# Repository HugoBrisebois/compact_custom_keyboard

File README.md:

## Compact Custom Keyboard

This is a compact Keyboard the is powered by a raspberry pi pico and is a hotswapable kailth choc mini keyswitches, the keyboard also has LEDs that can be used for a aestetic lighting and as light to see what you are typing.
The Keyboard is also a 60% keyboard meaning that it is quite small while not having too many layers like a 40% one.

# Features
- powered by a raspberry pi pico
- RGB LEDs
- kailth choc mini keyswitches
- 3d Printed keyswitches

# Reason for build this project
i wanted a keyboard that is completely custom to me and is also something that i can use in a cyberdeck project that i want to build later on. this keyboard is also perfect for everyday use and i am looking forward to using this keyboard too.

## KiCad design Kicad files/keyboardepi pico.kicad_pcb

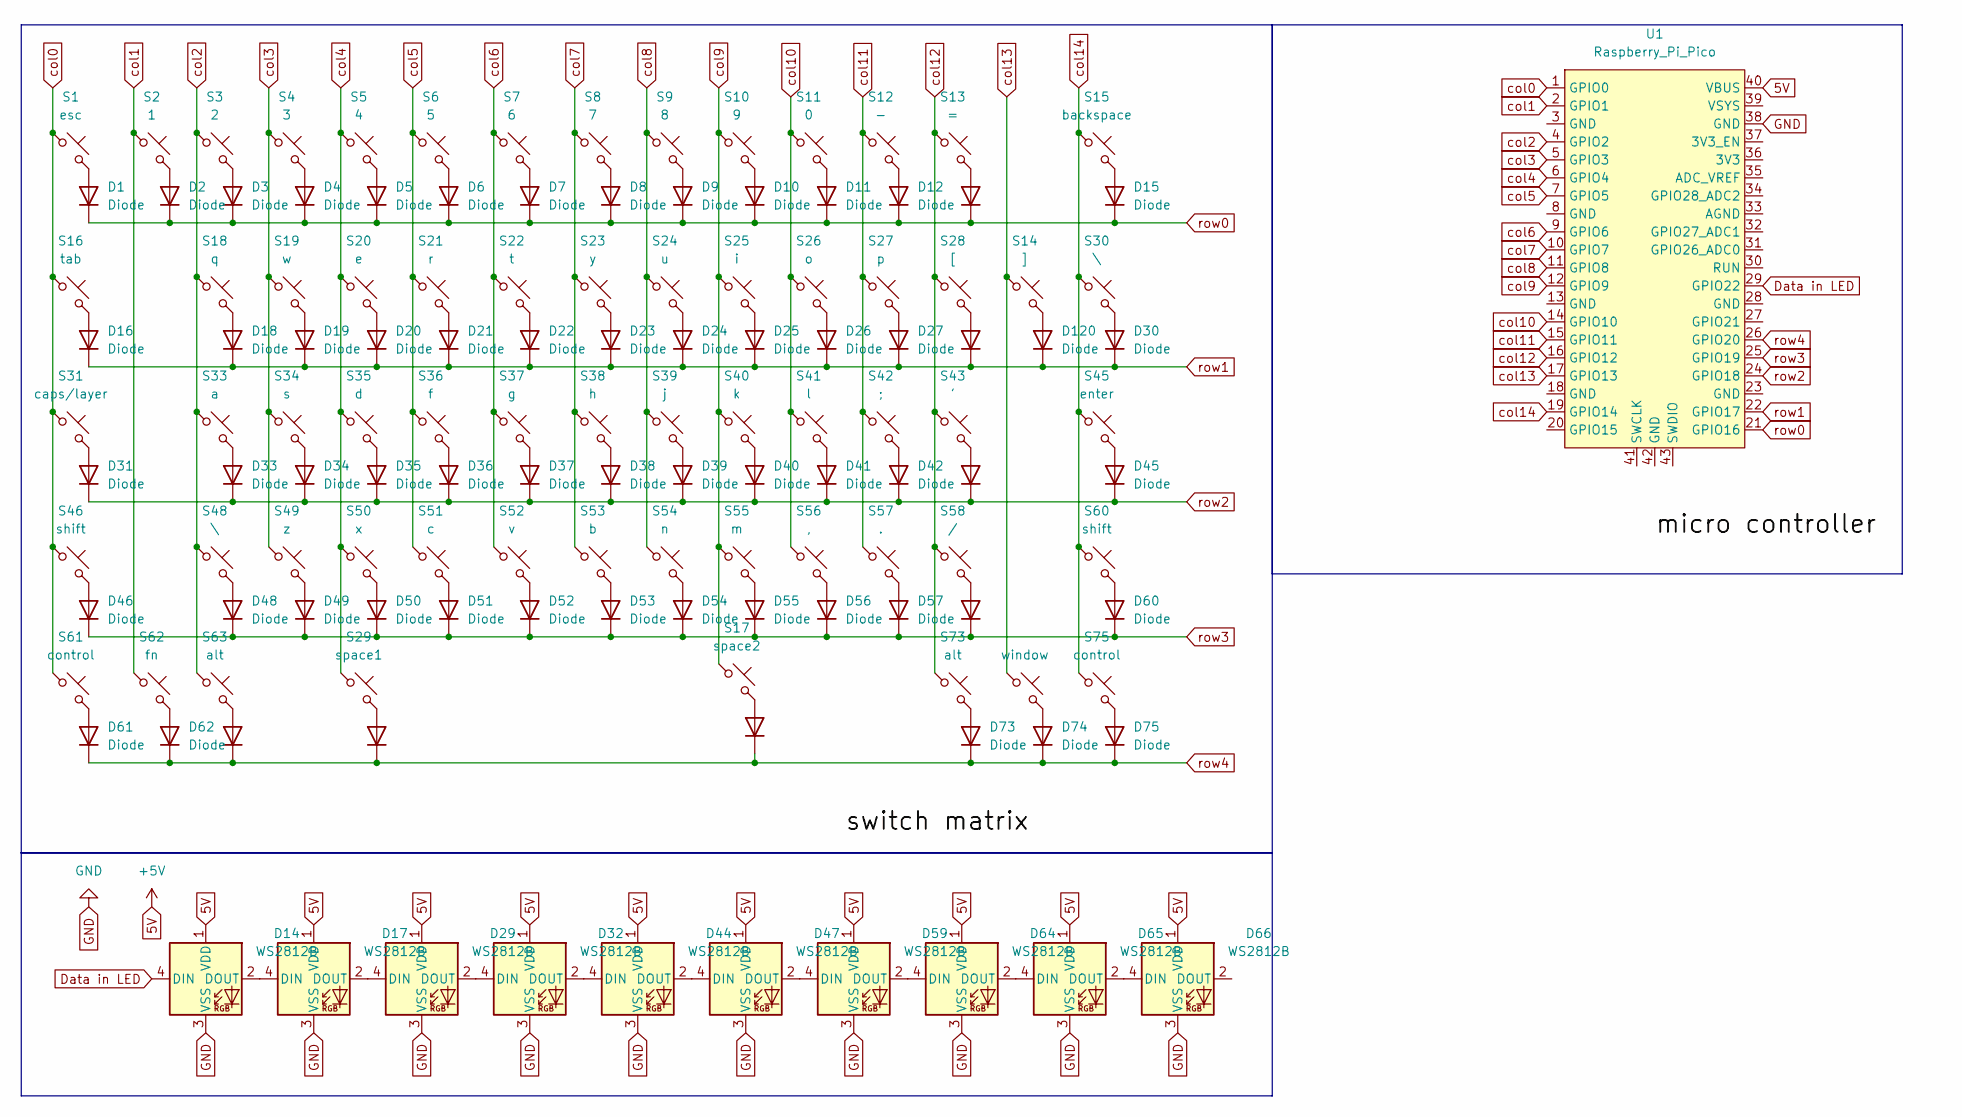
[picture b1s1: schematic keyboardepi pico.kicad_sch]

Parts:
D1, D2, D3, D4, D5, D6, D7, D8, D9, D10, D11, D12, D13, D15, D16, D18, D19, D20, D21, D22, D23, D24, D25, D26, D27, D28, D30, D31, D33, D34, D35, D36, D37, D38, D39, D40, D41, D42, D43, D45, D46, D48, D49, D50, D51, D52, D53, D54, D55, D56, D57, D58, D60, D61, D62, D63, D68, D73, D74, D75, D120, D121: Diode; Diode_DO-35
D14, D17, D29, D32, D44, D47, D59, D64, D65, D66: WS2812B; LED_WS2812B_PLCC4_5.0x5.0mm_P3.2mm
S1: esc; SW_Hotswap_Kailh_Choc_V1V2_1.00u
S2: 1; SW_Hotswap_Kailh_Choc_V1V2_1.00u
S3: 2; SW_Hotswap_Kailh_Choc_V1V2_1.00u
S4: 3; SW_Hotswap_Kailh_Choc_V1V2_1.00u
S5: 4; SW_Hotswap_Kailh_Choc_V1V2_1.00u
S6: 5; SW_Hotswap_Kailh_Choc_V1V2_1.00u
S7: 6; SW_Hotswap_Kailh_Choc_V1V2_1.00u
S8: 7; SW_Hotswap_Kailh_Choc_V1V2_1.00u
S9: 8; SW_Hotswap_Kailh_Choc_V1V2_1.00u
S10: 9; SW_Hotswap_Kailh_Choc_V1V2_1.00u
S11: 0; SW_Hotswap_Kailh_Choc_V1V2_1.00u
S12: -; SW_Hotswap_Kailh_Choc_V1V2_1.00u
S13: =; SW_Hotswap_Kailh_Choc_V1V2_1.00u
S14: ]; SW_Hotswap_Kailh_Choc_V1V2_1.00u
S15: backspace; SW_Hotswap_Kailh_Choc_V1V2_1.00u
S16: tab; SW_Hotswap_Kailh_Choc_V1V2_1.00u
S17: space2; SW_Hotswap_Kailh_Choc_V1V2_1.25u
S18: q; SW_Hotswap_Kailh_Choc_V1V2_1.00u
S19: w; SW_Hotswap_Kailh_Choc_V1V2_1.00u
S20: e; SW_Hotswap_Kailh_Choc_V1V2_1.00u
S21: r; SW_Hotswap_Kailh_Choc_V1V2_1.00u
S22: t; SW_Hotswap_Kailh_Choc_V1V2_1.00u
S23: y; SW_Hotswap_Kailh_Choc_V1V2_1.00u
S24: u; SW_Hotswap_Kailh_Choc_V1V2_1.00u
S25: i; SW_Hotswap_Kailh_Choc_V1V2_1.00u
S26: o; SW_Hotswap_Kailh_Choc_V1V2_1.00u
S27: p; SW_Hotswap_Kailh_Choc_V1V2_1.00u
S28: [; SW_Hotswap_Kailh_Choc_V1V2_1.00u
S29: space1; SW_Hotswap_Kailh_Choc_V1V2_1.25u
S30, S48: \; SW_Hotswap_Kailh_Choc_V1V2_1.00u
S31: caps/layer; SW_Hotswap_Kailh_Choc_V1V2_1.00u
S33: a; SW_Hotswap_Kailh_Choc_V1V2_1.00u
S34: s; SW_Hotswap_Kailh_Choc_V1V2_1.00u
S35: d; SW_Hotswap_Kailh_Choc_V1V2_1.00u
S36: f; SW_Hotswap_Kailh_Choc_V1V2_1.00u
S37: g; SW_Hotswap_Kailh_Choc_V1V2_1.00u
S38: h; SW_Hotswap_Kailh_Choc_V1V2_1.00u
S39: j; SW_Hotswap_Kailh_Choc_V1V2_1.00u
S40: k; SW_Hotswap_Kailh_Choc_V1V2_1.00u
S41: l; SW_Hotswap_Kailh_Choc_V1V2_1.00u
S42: ;; SW_Hotswap_Kailh_Choc_V1V2_1.00u
S43: '; SW_Hotswap_Kailh_Choc_V1V2_1.00u
S45: enter; SW_Hotswap_Kailh_Choc_V1V2_1.25u
S46: shift; SW_Hotswap_Kailh_Choc_V1V2_1.00u
S49: z; SW_Hotswap_Kailh_Choc_V1V2_1.00u
S50: x; SW_Hotswap_Kailh_Choc_V1V2_1.00u
S51: c; SW_Hotswap_Kailh_Choc_V1V2_1.00u
S52: v; SW_Hotswap_Kailh_Choc_V1V2_1.00u
S53: b; SW_Hotswap_Kailh_Choc_V1V2_1.00u
S54: n; SW_Hotswap_Kailh_Choc_V1V2_1.00u
S55: m; SW_Hotswap_Kailh_Choc_V1V2_1.00u
S56: ,; SW_Hotswap_Kailh_Choc_V1V2_1.00u
S57: .; SW_Hotswap_Kailh_Choc_V1V2_1.00u
S58: /; SW_Hotswap_Kailh_Choc_V1V2_1.00u
S60: shift; SW_Hotswap_Kailh_Choc_V1V2_1.25u
S61, S75: control; SW_Hotswap_Kailh_Choc_V1V2_1.00u
S62: fn; SW_Hotswap_Kailh_Choc_V1V2_1.00u
S63, S73: alt; SW_Hotswap_Kailh_Choc_V1V2_1.00u
S74: window; SW_Hotswap_Kailh_Choc_V1V2_1.00u
U1: Raspberry_Pi_Pico

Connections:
5V: D14.1 (VDD), D17.1 (VDD), D29.1 (VDD), D32.1 (VDD), D44.1 (VDD), D47.1 (VDD), D59.1 (VDD), D64.1 (VDD), D65.1 (VDD), D66.1 (VDD), U1.40 (VBUS)
Data in LED: D14.4 (DIN), U1.29 (GPIO22)
GND: D14.3 (VSS), D17.3 (VSS), D29.3 (VSS), D32.3 (VSS), D44.3 (VSS), D47.3 (VSS), D59.3 (VSS), D64.3 (VSS), D65.3 (VSS), D66.3 (VSS), U1.38 (GND)
unnamed: D1.2 (A), S1.2
unnamed: D2.2 (A), S2.2
unnamed: D3.2 (A), S3.2
unnamed: D4.2 (A), S4.2
unnamed: D5.2 (A), S5.2
unnamed: D6.2 (A), S6.2
unnamed: D7.2 (A), S7.2
unnamed: D8.2 (A), S8.2
unnamed: D9.2 (A), S9.2
unnamed: D10.2 (A), S10.2
unnamed: D11.2 (A), S11.2
unnamed: D12.2 (A), S12.2
unnamed: D13.2 (A), S13.2
unnamed: D14.2 (DOUT), D17.4 (DIN)
unnamed: D15.2 (A), S15.2
unnamed: D16.2 (A), S16.2
unnamed: D17.2 (DOUT), D29.4 (DIN)
unnamed: D18.2 (A), S18.2
unnamed: D19.2 (A), S19.2
unnamed: D20.2 (A), S20.2
unnamed: D21.2 (A), S21.2
unnamed: D22.2 (A), S22.2
unnamed: D23.2 (A), S23.2
unnamed: D24.2 (A), S24.2
unnamed: D25.2 (A), S25.2
unnamed: D26.2 (A), S26.2
unnamed: D27.2 (A), S27.2
unnamed: D28.2 (A), S28.2
unnamed: D29.2 (DOUT), D32.4 (DIN)
unnamed: D30.2 (A), S30.2
unnamed: D31.2 (A), S31.2
unnamed: D32.2 (DOUT), D44.4 (DIN)
unnamed: D33.2 (A), S33.2
unnamed: D34.2 (A), S34.2
unnamed: D35.2 (A), S35.2
unnamed: D36.2 (A), S36.2
unnamed: D37.2 (A), S37.2
unnamed: D38.2 (A), S38.2
unnamed: D39.2 (A), S39.2
unnamed: D40.2 (A), S40.2
unnamed: D41.2 (A), S41.2
unnamed: D42.2 (A), S42.2
unnamed: D43.2 (A), S43.2
unnamed: D44.2 (DOUT), D47.4 (DIN)
unnamed: D45.2 (A), S45.2
unnamed: D46.2 (A), S46.2
unnamed: D47.2 (DOUT), D59.4 (DIN)
unnamed: D48.2 (A), S48.2
unnamed: D49.2 (A), S49.2
unnamed: D50.2 (A), S50.2
unnamed: D51.2 (A), S51.2
unnamed: D52.2 (A), S52.2
unnamed: D53.2 (A), S53.2
unnamed: D54.2 (A), S54.2
unnamed: D55.2 (A), S55.2
unnamed: D56.2 (A), S56.2
unnamed: D57.2 (A), S57.2
unnamed: D58.2 (A), S58.2
unnamed: D59.2 (DOUT), D64.4 (DIN)
unnamed: D60.2 (A), S60.2
unnamed: D61.2 (A), S61.2
unnamed: D62.2 (A), S62.2
unnamed: D63.2 (A), S63.2
unnamed: D64.2 (DOUT), D65.4 (DIN)
unnamed: D65.2 (DOUT), D66.4 (DIN)
unnamed: D68.2 (A), S17.2
unnamed: D73.2 (A), S73.2
unnamed: D74.2 (A), S74.2
unnamed: D75.2 (A), S75.2
unnamed: D120.2 (A), S14.2
unnamed: D121.2 (A), S29.2
col0: S1.1, S16.1, S31.1, S46.1, S61.1, U1.1 (GPIO0)
col1: S2.1, S62.1, U1.2 (GPIO1)
col2: S3.1, S18.1, S33.1, S48.1, S63.1, U1.4 (GPIO2)
col3: S4.1, S19.1, S34.1, S49.1, U1.5 (GPIO3)
col4: S5.1, S20.1, S29.1, S35.1, S50.1, U1.6 (GPIO4)
col5: S6.1, S21.1, S36.1, S51.1, U1.7 (GPIO5)
col6: S7.1, S22.1, S37.1, S52.1, U1.9 (GPIO6)
col7: S8.1, S23.1, S38.1, S53.1, U1.10 (GPIO7)
col8: S9.1, S24.1, S39.1, S54.1, U1.11 (GPIO8)
col9: S10.1, S17.1, S25.1, S40.1, S55.1, U1.12 (GPIO9)
col10: S11.1, S26.1, S41.1, S56.1, U1.14 (GPIO10)
col11: S12.1, S27.1, S42.1, S57.1, U1.15 (GPIO11)
col12: S13.1, S28.1, S43.1, S58.1, S73.1, U1.16 (GPIO12)
col13: S14.1, S74.1, U1.17 (GPIO13)
col14: S15.1, S30.1, S45.1, S60.1, S75.1, U1.19 (GPIO14)
row0: D1.1 (K), D2.1 (K), D3.1 (K), D4.1 (K), D5.1 (K), D6.1 (K), D7.1 (K), D8.1 (K), D9.1 (K), D10.1 (K), D11.1 (K), D12.1 (K), D13.1 (K), D15.1 (K), U1.21 (GPIO16)
row1: D16.1 (K), D18.1 (K), D19.1 (K), D20.1 (K), D21.1 (K), D22.1 (K), D23.1 (K), D24.1 (K), D25.1 (K), D26.1 (K), D27.1 (K), D28.1 (K), D30.1 (K), D120.1 (K), U1.22 (GPIO17)
row2: D31.1 (K), D33.1 (K), D34.1 (K), D35.1 (K), D36.1 (K), D37.1 (K), D38.1 (K), D39.1 (K), D40.1 (K), D41.1 (K), D42.1 (K), D43.1 (K), D45.1 (K), U1.24 (GPIO18)
row3: D46.1 (K), D48.1 (K), D49.1 (K), D50.1 (K), D51.1 (K), D52.1 (K), D53.1 (K), D54.1 (K), D55.1 (K), D56.1 (K), D57.1 (K), D58.1 (K), D60.1 (K), U1.25 (GPIO19)
row4: D61.1 (K), D62.1 (K), D63.1 (K), D68.1 (K), D73.1 (K), D74.1 (K), D75.1 (K), D121.1 (K), U1.26 (GPIO20)

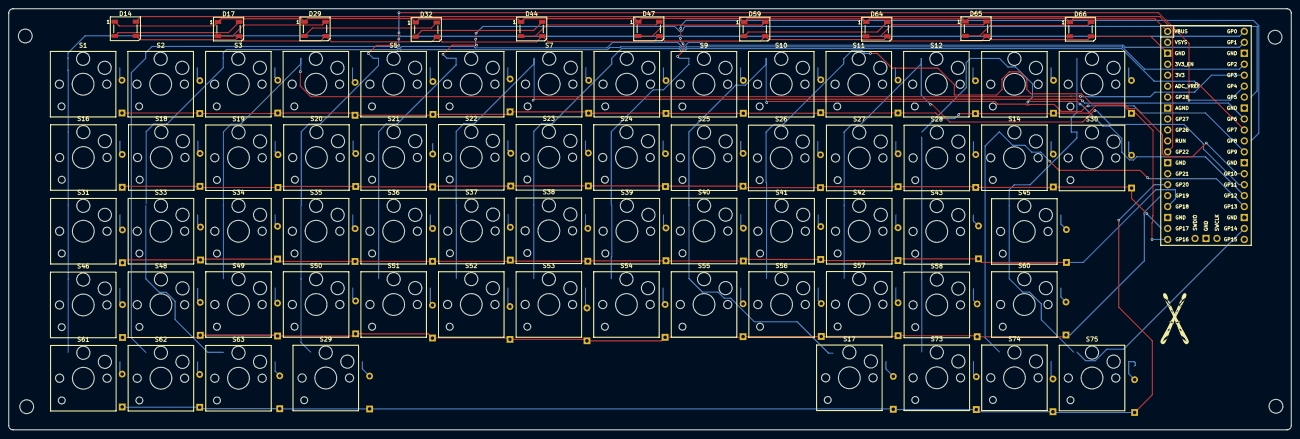
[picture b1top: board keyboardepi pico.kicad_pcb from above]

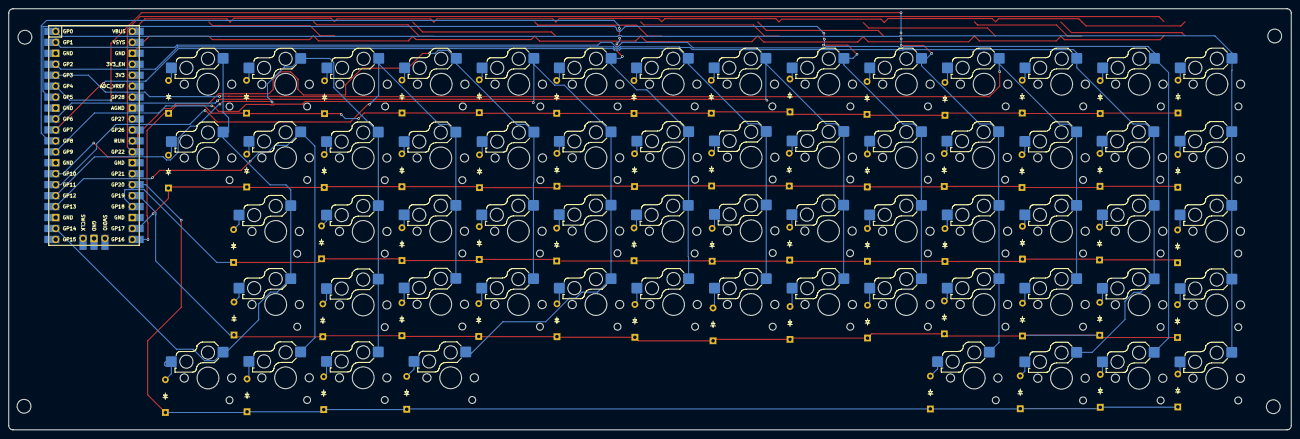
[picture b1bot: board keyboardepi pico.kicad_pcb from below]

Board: 2 copper layers, 297.5 x 97.7 mm, 135 parts (63 on the bottom side), 94 nets.

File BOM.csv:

Reference,Qty,Value,DNP,Exclude from BOM,Exclude from Board,Footprint,Datasheet,,Price,Website,
"D1,D2,D3,D4,D5,D6,D7,D8,D9,D10,D11,D12,D13,D15,D16,D18,D19,D20,D21,D22,D23,D24,D25,D26,D27,D28,D30,D31,D33,D34,D35,D36,D37,D38,D39,D40,D41,D42,D43,D45,D46,D48,D49,D50,D51,D52,D53,D54,D55,D56,D57,D58,D60,D61,D62,D63,D68,D73,D74,D75,D120,D121",62,Diode,,,,Diode_SMD:D_SOD-123F,,,$1.41 ,https://www.aliexpress.com/item/1005007536859190.html?spm=a2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,
"D14,D17,D29,D32,D44,D47,D59,D64,D65,D66",10,WS2812B,,,,LED_SMD:LED_WS2812B_PLCC4_5.0x5.0mm_P3.2mm,https://cdn-shop.adafruit.com/datasheets/WS2812B.pdf,,$1.74 ,https://www.aliexpress.com/item/1005001376489095.html?spm=a2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,
S1,1,esc,,,,PCM_Switch_Keyboard_Hotswap_Kailh:SW_Hotswap_Kailh_Choc_V1V2_1.00u,~,,,0.35,unit price
S2,1,1,,,,PCM_Switch_Keyboard_Hotswap_Kailh:SW_Hotswap_Kailh_Choc_V1V2_1.00u,~,,,0.35,unit price
S3,1,2,,,,PCM_Switch_Keyboard_Hotswap_Kailh:SW_Hotswap_Kailh_Choc_V1V2_1.00u,~,,,0.35,unit price
S4,1,3,,,,PCM_Switch_Keyboard_Hotswap_Kailh:SW_Hotswap_Kailh_Choc_V1V2_1.00u,~,,,0.35,unit price
S5,1,4,,,,PCM_Switch_Keyboard_Hotswap_Kailh:SW_Hotswap_Kailh_Choc_V1V2_1.00u,~,,,0.35,unit price
S6,1,5,,,,PCM_Switch_Keyboard_Hotswap_Kailh:SW_Hotswap_Kailh_Choc_V1V2_1.00u,~,,,0.35,unit price
S7,1,6,,,,PCM_Switch_Keyboard_Hotswap_Kailh:SW_Hotswap_Kailh_Choc_V1V2_1.00u,~,,,0.35,unit price
S8,1,7,,,,PCM_Switch_Keyboard_Hotswap_Kailh:SW_Hotswap_Kailh_Choc_V1V2_1.00u,~,,,0.35,unit price
S9,1,8,,,,PCM_Switch_Keyboard_Hotswap_Kailh:SW_Hotswap_Kailh_Choc_V1V2_1.00u,~,,,0.35,unit price
S10,1,9,,,,PCM_Switch_Keyboard_Hotswap_Kailh:SW_Hotswap_Kailh_Choc_V1V2_1.00u,~,,,0.35,unit price
S11,1,0,,,,PCM_Switch_Keyboard_Hotswap_Kailh:SW_Hotswap_Kailh_Choc_V1V2_1.00u,~,,,0.35,unit price
S12,1,-,,,,PCM_Switch_Keyboard_Hotswap_Kailh:SW_Hotswap_Kailh_Choc_V1V2_1.00u,~,,,0.35,unit price
S13,1,=,,,,PCM_Switch_Keyboard_Hotswap_Kailh:SW_Hotswap_Kailh_Choc_V1V2_1.00u,~,,,0.35,unit price
S14,1,],,,,PCM_Switch_Keyboard_Hotswap_Kailh:SW_Hotswap_Kailh_Choc_V1V2_1.00u,~,,,0.35,unit price
S15,1,backspace,,,,PCM_Switch_Keyboard_Hotswap_Kailh:SW_Hotswap_Kailh_Choc_V1V2_1.00u,~,,,0.35,unit price
S16,1,tab,,,,PCM_Switch_Keyboard_Hotswap_Kailh:SW_Hotswap_Kailh_Choc_V1V2_1.00u,~,,,0.35,unit price
S17,1,space2,,,,PCM_Switch_Keyboard_Hotswap_Kailh:SW_Hotswap_Kailh_Choc_V1V2_1.25u,~,,,0.35,unit price
S18,1,q,,,,PCM_Switch_Keyboard_Hotswap_Kailh:SW_Hotswap_Kailh_Choc_V1V2_1.00u,~,,,0.35,unit price
S19,1,w,,,,PCM_Switch_Keyboard_Hotswap_Kailh:SW_Hotswap_Kailh_Choc_V1V2_1.00u,~,,,0.35,unit price
S20,1,e,,,,PCM_Switch_Keyboard_Hotswap_Kailh:SW_Hotswap_Kailh_Choc_V1V2_1.00u,~,,,0.35,unit price
S21,1,r,,,,PCM_Switch_Keyboard_Hotswap_Kailh:SW_Hotswap_Kailh_Choc_V1V2_1.00u,~,,,0.35,unit price
S22,1,t,,,,PCM_Switch_Keyboard_Hotswap_Kailh:SW_Hotswap_Kailh_Choc_V1V2_1.00u,~,,,0.35,unit price
S23,1,y,,,,PCM_Switch_Keyboard_Hotswap_Kailh:SW_Hotswap_Kailh_Choc_V1V2_1.00u,~,,,0.35,unit price
S24,1,u,,,,PCM_Switch_Keyboard_Hotswap_Kailh:SW_Hotswap_Kailh_Choc_V1V2_1.00u,~,,,0.35,unit price
S25,1,i,,,,PCM_Switch_Keyboard_Hotswap_Kailh:SW_Hotswap_Kailh_Choc_V1V2_1.00u,~,,,0.35,unit price
S26,1,o,,,,PCM_Switch_Keyboard_Hotswap_Kailh:SW_Hotswap_Kailh_Choc_V1V2_1.00u,~,,,0.35,unit price
S27,1,p,,,,PCM_Switch_Keyboard_Hotswap_Kailh:SW_Hotswap_Kailh_Choc_V1V2_1.00u,~,,,0.35,unit price
S28,1,[,,,,PCM_Switch_Keyboard_Hotswap_Kailh:SW_Hotswap_Kailh_Choc_V1V2_1.00u,~,,,0.35,unit price
S29,1,space1,,,,PCM_Switch_Keyboard_Hotswap_Kailh:SW_Hotswap_Kailh_Choc_V1V2_1.25u,~,,,0.35,unit price
"S30,S48",2,\,,,,PCM_Switch_Keyboard_Hotswap_Kailh:SW_Hotswap_Kailh_Choc_V1V2_1.00u,~,,,0.35,unit price
S31,1,caps/layer,,,,PCM_Switch_Keyboard_Hotswap_Kailh:SW_Hotswap_Kailh_Choc_V1V2_1.00u,~,,,0.35,unit price
S33,1,a,,,,PCM_Switch_Keyboard_Hotswap_Kailh:SW_Hotswap_Kailh_Choc_V1V2_1.00u,~,,,0.35,unit price
S34,1,s,,,,PCM_Switch_Keyboard_Hotswap_Kailh:SW_Hotswap_Kailh_Choc_V1V2_1.00u,~,,,0.35,unit price
S35,1,d,,,,PCM_Switch_Keyboard_Hotswap_Kailh:SW_Hotswap_Kailh_Choc_V1V2_1.00u,~,,,0.35,unit price
S36,1,f,,,,PCM_Switch_Keyboard_Hotswap_Kailh:SW_Hotswap_Kailh_Choc_V1V2_1.00u,~,,,0.35,unit price
S37,1,g,,,,PCM_Switch_Keyboard_Hotswap_Kailh:SW_Hotswap_Kailh_Choc_V1V2_1.00u,~,,,0.35,unit price
S38,1,h,,,,PCM_Switch_Keyboard_Hotswap_Kailh:SW_Hotswap_Kailh_Choc_V1V2_1.00u,~,,,0.35,unit price
S39,1,j,,,,PCM_Switch_Keyboard_Hotswap_Kailh:SW_Hotswap_Kailh_Choc_V1V2_1.00u,~,,,0.35,unit price
S40,1,k,,,,PCM_Switch_Keyboard_Hotswap_Kailh:SW_Hotswap_Kailh_Choc_V1V2_1.00u,~,,,0.35,unit price
S41,1,l,,,,PCM_Switch_Keyboard_Hotswap_Kailh:SW_Hotswap_Kailh_Choc_V1V2_1.00u,~,,,0.35,unit price
S42,1,;,,,,PCM_Switch_Keyboard_Hotswap_Kailh:SW_Hotswap_Kailh_Choc_V1V2_1.00u,~,,,0.35,unit price
S43,1,',,,,PCM_Switch_Keyboard_Hotswap_Kailh:SW_Hotswap_Kailh_Choc_V1V2_1.00u,~,,,0.35,unit price
S45,1,enter,,,,PCM_Switch_Keyboard_Hotswap_Kailh:SW_Hotswap_Kailh_Choc_V1V2_1.25u,~,,,0.35,unit price
S46,1,shift,,,,PCM_Switch_Keyboard_Hotswap_Kailh:SW_Hotswap_Kailh_Choc_V1V2_1.00u,~,,,0.35,unit price
S49,1,z,,,,PCM_Switch_Keyboard_Hotswap_Kailh:SW_Hotswap_Kailh_Choc_V1V2_1.00u,~,,,0.35,unit price
S50,1,x,,,,PCM_Switch_Keyboard_Hotswap_Kailh:SW_Hotswap_Kailh_Choc_V1V2_1.00u,~,,,0.35,unit price
S51,1,c,,,,PCM_Switch_Keyboard_Hotswap_Kailh:SW_Hotswap_Kailh_Choc_V1V2_1.00u,~,,,0.35,unit price
S52,1,v,,,,PCM_Switch_Keyboard_Hotswap_Kailh:SW_Hotswap_Kailh_Choc_V1V2_1.00u,~,,,0.35,unit price
S53,1,b,,,,PCM_Switch_Keyboard_Hotswap_Kailh:SW_Hotswap_Kailh_Choc_V1V2_1.00u,~,,,0.35,unit price
S54,1,n,,,,PCM_Switch_Keyboard_Hotswap_Kailh:SW_Hotswap_Kailh_Choc_V1V2_1.00u,~,,,0.35,unit price
S55,1,m,,,,PCM_Switch_Keyboard_Hotswap_Kailh:SW_Hotswap_Kailh_Choc_V1V2_1.00u,~,,,0.35,unit price
S56,1,",",,,,PCM_Switch_Keyboard_Hotswap_Kailh:SW_Hotswap_Kailh_Choc_V1V2_1.00u,~,,,0.35,unit price
S57,1,.,,,,PCM_Switch_Keyboard_Hotswap_Kailh:SW_Hotswap_Kailh_Choc_V1V2_1.00u,~,,,0.35,unit price
S58,1,/,,,,PCM_Switch_Keyboard_Hotswap_Kailh:SW_Hotswap_Kailh_Choc_V1V2_1.00u,~,,,0.35,unit price
S60,1,shift,,,,PCM_Switch_Keyboard_Hotswap_Kailh:SW_Hotswap_Kailh_Choc_V1V2_1.25u,~,,,0.35,unit price
"S61,S75",2,control,,,,PCM_Switch_Keyboard_Hotswap_Kailh:SW_Hotswap_Kailh_Choc_V1V2_1.00u,~,,,0.35,unit price
S62,1,fn,,,,PCM_Switch_Keyboard_Hotswap_Kailh:SW_Hotswap_Kailh_Choc_V1V2_1.00u,~,,,0.35,unit price
"S63,S73",2,alt,,,,PCM_Switch_Keyboard_Hotswap_Kailh:SW_Hotswap_Kailh_Choc_V1V2_1.00u,~,,,0.35,unit price
S74,1,window,,,,PCM_Switch_Keyboard_Hotswap_Kailh:SW_Hotswap_Kailh_Choc_V1V2_1.00u,~,,,0.35,unit price
U1,1,Raspberry_Pi_Pico,,,,ScottoKeebs_MCU:Raspberry_Pi_Pico,,,$1.59 ,https://www.aliexpress.com/item/1005008379427391.html?spm=a2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,
,,,,,,,,,,,
PCB Total Cost,,,,,,,,,$30.25 ,,
,,,,,,,,,,,
Total Keyswitches,,,62,,,,,,$24.50 ,https://www.aliexpress.us/item/3256808620484354.html?spm=a2g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,
,,,,,,,,,(First Purchase discount),,
Total Hotswap sockets,,,62,,,,,,$8.32 ,https://www.aliexpress.com/item/1005009312876316.html?spm=a2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,
,,,,,,,,,,,
,,,,,Total Cost,,,,$67.81 ,,

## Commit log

2025-12-29 Uploaded Schematics and kicad files
2025-12-29 organized the directories for the Kicad files
2025-12-29 Updated the PCB
2025-12-29 Finished the BOM
2025-12-29 finalizing the project for shipping
2025-12-29 adding the case files
2025-12-29 added case file
    added the file with only the case in it
2025-12-29 Removed the LEDs
2025-12-29 fixing the PCB
2025-12-29 fixing files and folders
2025-12-30 added my logo to the pcb
2025-12-30 Add project details for compact custom keyboard
    Added detailed information about the compact custom keyboard project, including features and reasons for building it.
2025-12-30 finishing up to ship the project
2025-12-30 made it easy to get started with the keyboard
2025-12-31 added the firmware although it probably won't work
2026-01-10 fixing somethings to ship
2026-01-10 added the asembly .obj
2026-01-21 renamed an image file
2026-01-21 moving the case.png and removing the journal to re-upload it
2026-01-21 made sure that the GBR has drl files as well as has the GBR
2026-01-22 changed the files so that they are .step files
2026-01-22 Revise user guide for Compact Keyboard
    Updated user guide to correct keyboard name and improve clarity.
2026-01-27 fixed pricing
2026-02-12 Modify BOM.csv to include new parts and costs
    Updated BOM.csv to add new components and adjust pricing.
2026-02-12 Update BOM.csv to add new entries and costs
2026-06-16 rebuilding gbr files and pcb for better soldering ease
2026-06-16 rebuilding the gbr files
